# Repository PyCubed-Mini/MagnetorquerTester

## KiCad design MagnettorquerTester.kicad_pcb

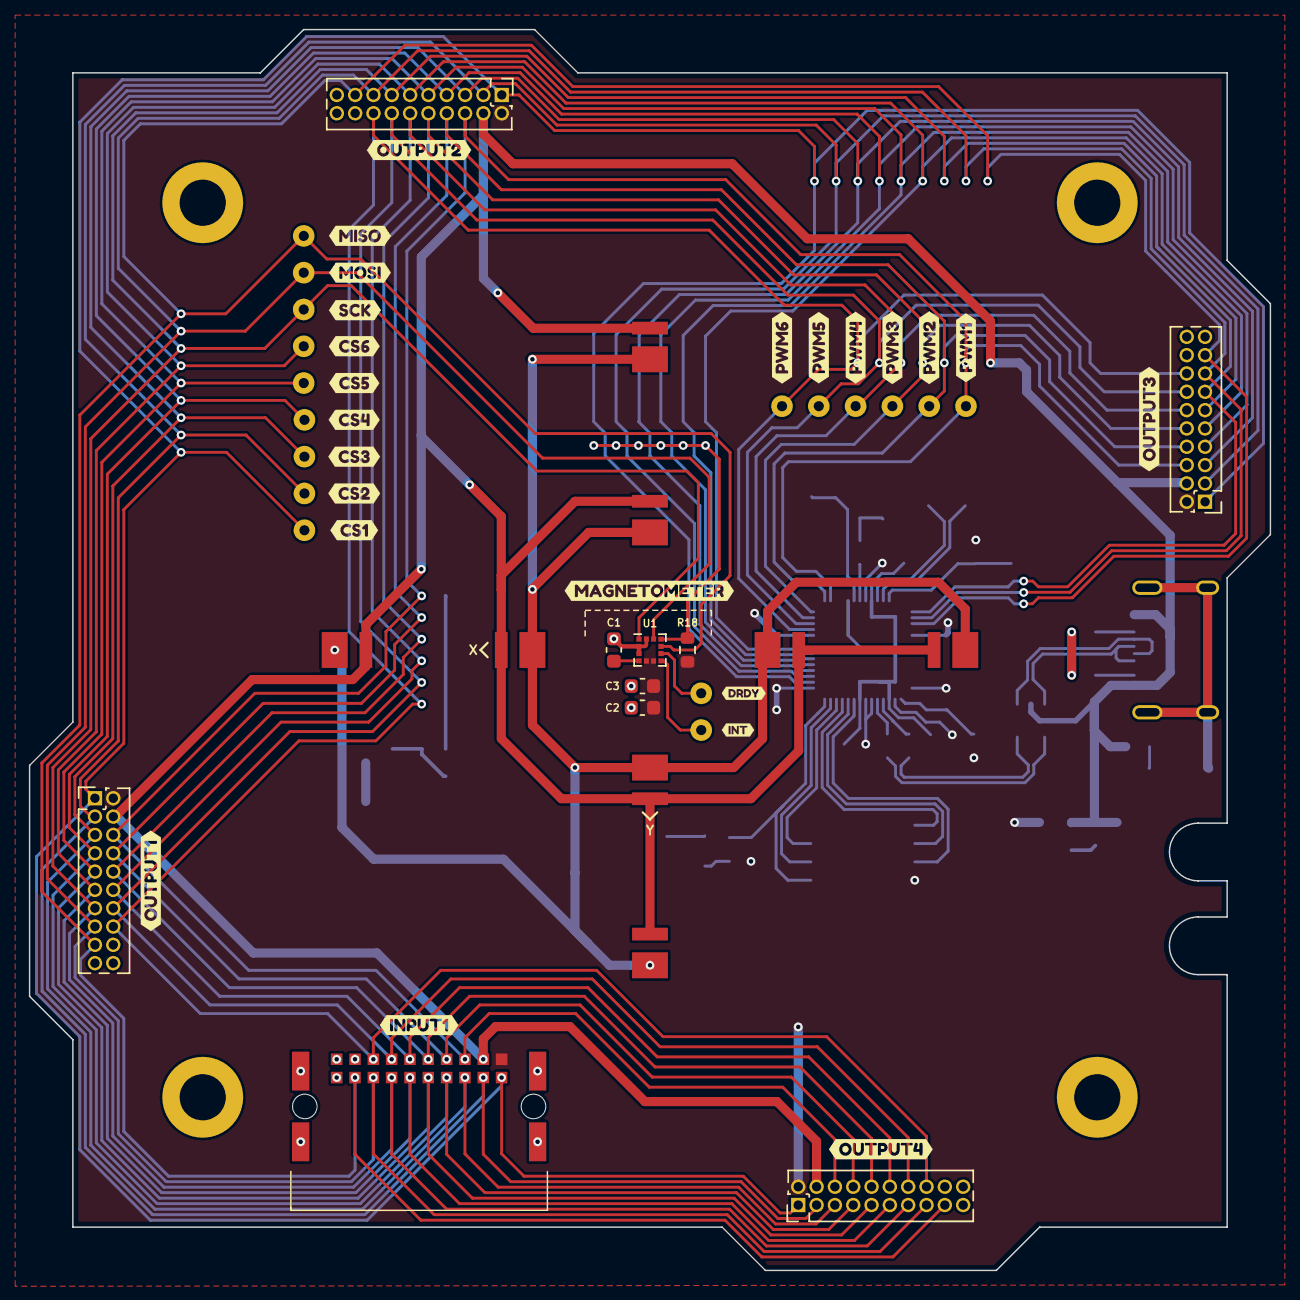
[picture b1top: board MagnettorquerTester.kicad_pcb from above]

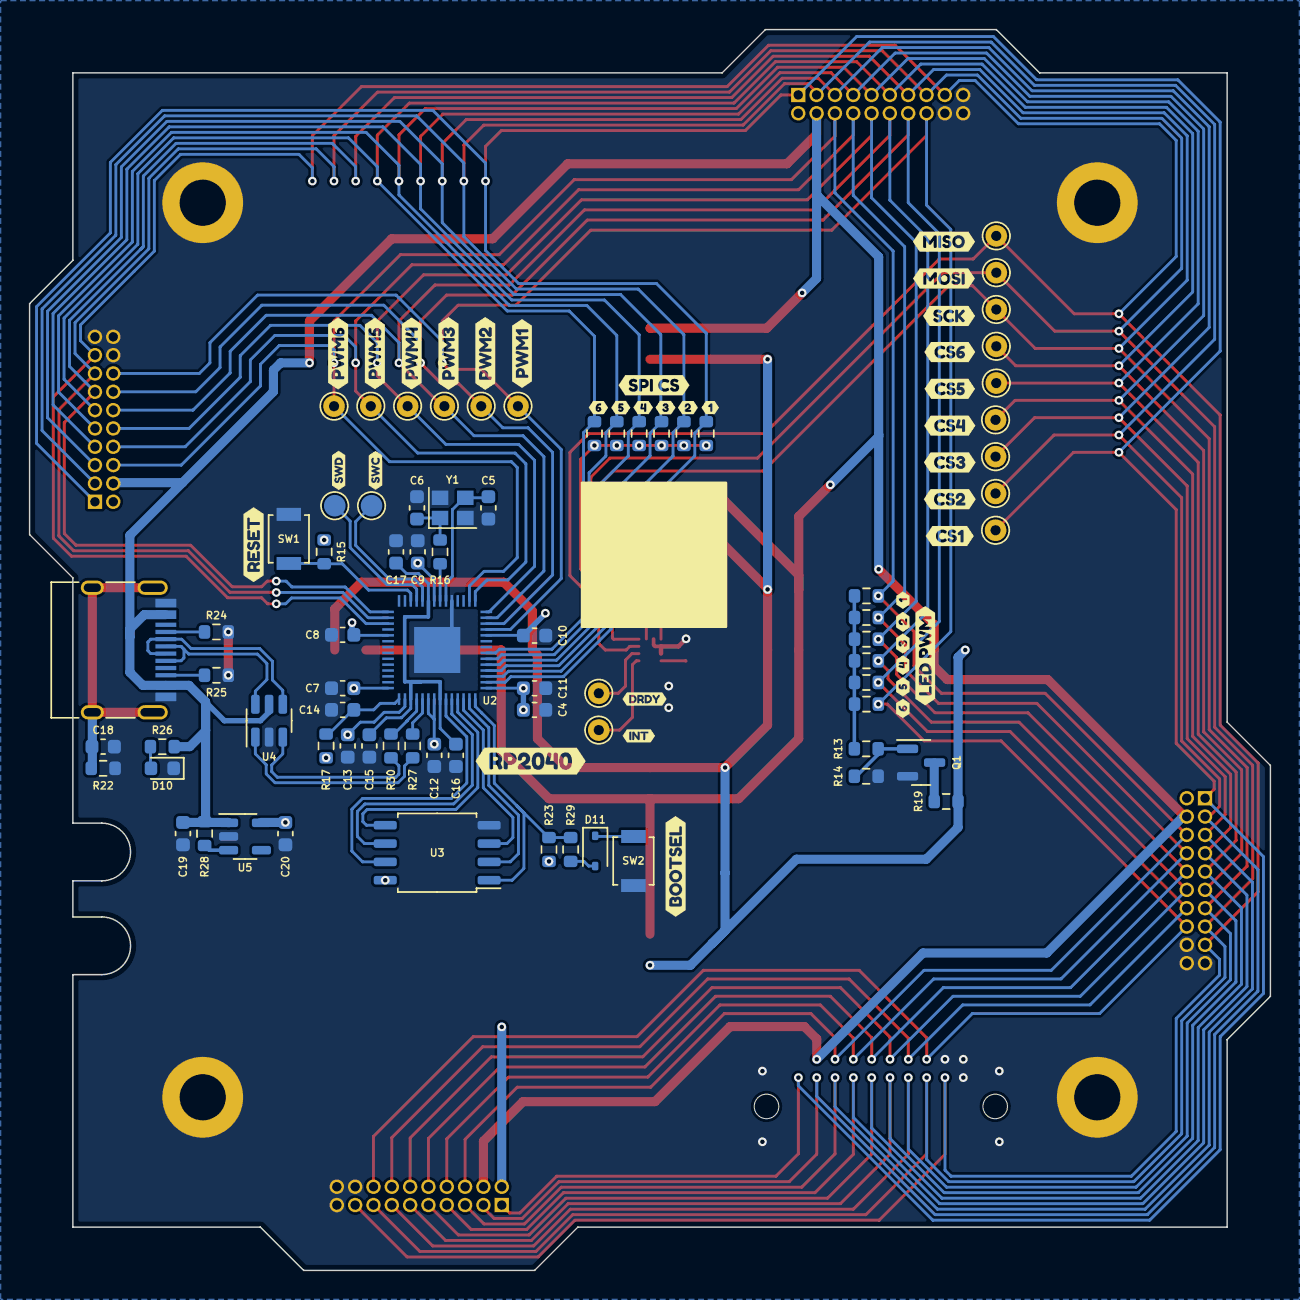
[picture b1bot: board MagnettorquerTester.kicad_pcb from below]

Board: 2 copper layers, 86.0 x 86.0 mm, 156 parts (111 on the bottom side), 53 nets.

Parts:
C1, C3, C7, C8, C9, C10, C11, C12, C13, C16, C17: 0.1uF; C_0603_1608Metric
C2, C4, C14, C15, C19, C20: 1uF; C_0603_1608Metric
C5, C6: 22pF; C_0603_1608Metric
C18: 4.7nF; C_0603_1608Metric
D1, D2, D3, D4, D5, D6, D7, D8: White; LED_WL-SWTP_WRE
D10: Green; LED_0603_1608Metric
D11: D_Schottky; D_SOD-323
H1, H2, H3, H4: MountingHole_Pad; MountingHole_3.2mm_M3_DIN965_Pad
J1: Out Conn 1; PinHeader_2x10_P1.27mm_Vertical
J2: Out Conn 2; PinHeader_2x10_P1.27mm_Vertical
J3: Out Conn 3; PinHeader_2x10_P1.27mm_Vertical
J4: Out Conn 4; PinHeader_2x10_P1.27mm_Vertical
J5: In Conn; M556102042R
J6: USB-C Receptacle; USB_C_Receptacle_HRO_TYPE-C-31-M-12
Q1: BSS138; SOT-23
R1, R2, R3, R4, R5, R6, R7, R8, R9, R10, R11, R12, R17, R19: 0; R_0603_1608Metric
R13: 220; R_0603_1608Metric
R14, R15, R18, R23: 10K; R_0603_1608Metric
R16, R26, R29: 1K; R_0603_1608Metric
R22: 1M; R_0603_1608Metric
R24, R25: 5.1K; R_0603_1608Metric
R27, R30: 27.4; R_0603_1608Metric
R28: 100K; R_0603_1608Metric
Ref**: Val**; pycubed_mini_half
SW1: Reset; SW_SPST_B3U-1000P
SW2: BOOTSEL; SW_SPST_B3U-1000P
TP1: INT; TestPoint_THTPad_D1.5mm_Drill0.7mm
TP2: DRDY; TestPoint_THTPad_D1.5mm_Drill0.7mm
TP3: PWM1; TestPoint_THTPad_D1.5mm_Drill0.7mm
TP4: PWM2; TestPoint_THTPad_D1.5mm_Drill0.7mm
TP5: PWM3; TestPoint_THTPad_D1.5mm_Drill0.7mm
TP6: PWM4; TestPoint_THTPad_D1.5mm_Drill0.7mm
TP7: PWM5; TestPoint_THTPad_D1.5mm_Drill0.7mm
TP8: PWM6; TestPoint_THTPad_D1.5mm_Drill0.7mm
TP9: SPI_SCK; TestPoint_THTPad_D1.5mm_Drill0.7mm
TP10: SPI_MOSI; TestPoint_THTPad_D1.5mm_Drill0.7mm
TP11: SPI_MISO; TestPoint_THTPad_D1.5mm_Drill0.7mm
TP12: SPI_CS1; TestPoint_THTPad_D1.5mm_Drill0.7mm
TP13: SPI_CS2; TestPoint_THTPad_D1.5mm_Drill0.7mm
TP14: SPI_CS3; TestPoint_THTPad_D1.5mm_Drill0.7mm
TP15: SPI_CS4; TestPoint_THTPad_D1.5mm_Drill0.7mm
TP16: SPI_CS5; TestPoint_THTPad_D1.5mm_Drill0.7mm
TP17: SPI_CS6; TestPoint_THTPad_D1.5mm_Drill0.7mm
TP18: SWCLK; TestPoint_Pad_D1.5mm
TP19: SWDIO; TestPoint_Pad_D1.5mm
U1: LIS3MDL; LGA-12_2x2mm_P0.5mm
U2: RP2040; IC57_RP2040
U3: W25Q32JVSS; SOIC-8_5.23x5.23mm_P1.27mm
U4: USBLC6-2SC6; SOT-23-6
U5: AP2112K-3.3; SOT-23-5
Y1: 12MHz; Crystal_SMD_2520-4Pin_2.5x2.0mm
kibuzzard-64532B72: G***; kibuzzard-64532B72
kibuzzard-64532BB5, kibuzzard-64532BB5#2: G***; kibuzzard-64532BB5
kibuzzard-64532BBA, kibuzzard-64532BBA#2: G***; kibuzzard-64532BBA
kibuzzard-64532BCA, kibuzzard-64532BCA#2: G***; kibuzzard-64532BCA
kibuzzard-64532BCE, kibuzzard-64532BCE#2: G***; kibuzzard-64532BCE
kibuzzard-64532BD1, kibuzzard-64532BD1#2: G***; kibuzzard-64532BD1
kibuzzard-64532BD5, kibuzzard-64532BD5#2: G***; kibuzzard-64532BD5
kibuzzard-64532C69: G***; kibuzzard-64532C69
kibuzzard-64532E75: G***; kibuzzard-64532E75
kibuzzard-64532FC8: G***; kibuzzard-64532FC8
kibuzzard-64532FCD: G***; kibuzzard-64532FCD
kibuzzard-645310D5, kibuzzard-645310D5#2: G***; kibuzzard-645310D5
kibuzzard-645321C3, kibuzzard-645321C3#2: G***; kibuzzard-645321C3
kibuzzard-645321D8, kibuzzard-645321D8#2: G***; kibuzzard-645321D8
kibuzzard-645321E4, kibuzzard-645321E4#2: G***; kibuzzard-645321E4
kibuzzard-645321EC, kibuzzard-645321EC#2: G***; kibuzzard-645321EC
kibuzzard-645321F5, kibuzzard-645321F5#2: G***; kibuzzard-645321F5
kibuzzard-645321FE, kibuzzard-645321FE#2: G***; kibuzzard-645321FE
kibuzzard-645322DE, kibuzzard-645322DE#2: G***; kibuzzard-645322DE
kibuzzard-645323A0, kibuzzard-645323A0#2: G***; kibuzzard-645323A0
kibuzzard-645323A5, kibuzzard-645323A5#2: G***; kibuzzard-645323A5
kibuzzard-645333A6: G***; kibuzzard-645333A6
kibuzzard-6453239A, kibuzzard-6453239A#2: G***; kibuzzard-6453239A
kibuzzard-6453269D: G***; kibuzzard-6453269D
kibuzzard-6453278C, kibuzzard-6453278C#2: G***; kibuzzard-6453278C
kibuzzard-6453285D: G***; kibuzzard-6453285D
kibuzzard-6453286D: G***; kibuzzard-6453286D
kibuzzard-64531072, kibuzzard-64531072#2: G***; kibuzzard-64531072
kibuzzard-64532206, kibuzzard-64532206#2: G***; kibuzzard-64532206
kibuzzard-64532321: G***; kibuzzard-64532321
kibuzzard-64532386, kibuzzard-64532386#2: G***; kibuzzard-64532386
kibuzzard-64532395, kibuzzard-64532395#2: G***; kibuzzard-64532395
kibuzzard-64532783, kibuzzard-64532783#2: G***; kibuzzard-64532783
kibuzzard-64532824: G***; kibuzzard-64532824
kibuzzard-64532894: G***; kibuzzard-64532894
kibuzzard-64533294: G***; kibuzzard-64533294

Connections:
+1V1: C15.1, C16.1, C17.1, U2.23 (DVDD), U2.45 (VREG_VOUT), U2.50 (DVDD)
+3V3: C2.1, C3.1, C4.1, C7.1, C8.1, C9.1, C10.1, C11.1, C12.1, C13.1, C20.1, J1.2, J2.2, J3.2, J4.2, J5.2, R15.1, R17.2, R18.1, R23.1, U1.5 (Vdd), U1.6 (Vdd_IO), U2.1 (IOVDD), U2.10 (IOVDD), U2.22 (IOVDD), U2.33 (IOVDD), U2.42 (IOVDD), U2.44 (VREG_VIN), U2.48 (USB_VDD), U2.49 (IOVDD), U3.8 (VCC), U5.5 (VOUT)
/AREF: C14.2, R17.1, U2.43 (ADC_AVDD)
/DRDY: TP2.1, U1.8 (DRDY)
/INT: TP1.1, U1.7 (INT)
/PWM: R7.2, R8.2, R9.2, R10.2, R11.2, R12.2, R13.1
/PWM1: J1.6, J2.6, J3.6, J4.6, J5.6, R7.1, TP3.1, U2.16 (GPIO13)
/PWM2: J1.8, J2.8, J3.8, J4.8, J5.8, R8.1, TP4.1, U2.15 (GPIO12)
/PWM3: J1.10, J2.10, J3.10, J4.10, J5.10, R9.1, TP5.1, U2.14 (GPIO11)
/PWM4: J1.12, J2.12, J3.12, J4.12, J5.12, R10.1, TP6.1, U2.13 (GPIO10)
/PWM5: J1.14, J2.14, J3.14, J4.14, J5.14, R11.1, TP7.1, U2.12 (GPIO9)
/PWM6: J1.16, J2.16, J3.16, J4.16, J5.16, R12.1, TP8.1, U2.11 (GPIO8)
/QSPI_CS: R23.2, R29.1, U2.56 (QSPI_CSN), U3.1 (~CS)
/QSPI_DATA0: U2.53 (QSPI_SD0), U3.5 (DI(IO0))
/QSPI_DATA1: U2.55 (QSPI_SD1), U3.2 (DO(IO1))
/QSPI_DATA2: U2.54 (QSPI_SD2), U3.3 (IO2)
/QSPI_DATA3: U2.51 (QSPI_SD3), U3.7 (IO3)
/QSPI_SCK: U2.52 (QSPI_SCLK), U3.6 (CLK)
/RESET: R15.2, SW1.2 (B), U2.26 (RUN)
/SPI_CS: R1.2, R2.2, R3.2, R4.2, R5.2, R6.2, R18.2, U1.10 (~CS)
/SPI_CS1: J1.1, J2.1, J3.1, J4.1, J5.1, R1.1, TP12.1, U2.2 (GPIO0)
/SPI_CS2: J1.3, J2.3, J3.3, J4.3, J5.3, R2.1, TP13.1, U2.3 (GPIO1)
/SPI_CS3: J1.5, J2.5, J3.5, J4.5, J5.5, R3.1, TP14.1, U2.4 (GPIO2)
/SPI_CS4: J1.7, J2.7, J3.7, J4.7, J5.7, R4.1, TP15.1, U2.5 (GPIO3)
/SPI_CS5: J1.9, J2.9, J3.9, J4.9, J5.9, R5.1, TP16.1, U2.6 (GPIO4)
/SPI_CS6: J1.11, J2.11, J3.11, J4.11, J5.11, R6.1, TP17.1, U2.7 (GPIO5)
/SPI_MISO: J1.17, J2.17, J3.17, J4.17, J5.17, TP11.1, U1.9 (SDO/SA1), U2.31 (GPIO20)
/SPI_MOSI: J1.15, J2.15, J3.15, J4.15, J5.15, TP10.1, U1.11 (SDA/SDI/SDO), U2.30 (GPIO19)
/SPI_SCK: J1.13, J2.13, J3.13, J4.13, J5.13, TP9.1, U1.1 (SCL/SPC), U2.29 (GPIO18)
/SWCLK: TP18.1, U2.24 (SWCLK)
/SWDIO: TP19.1, U2.25 (SWD)
DBus+: J6.A6 (D+), J6.B6 (D+), U4.6 (I/O1)
DBus-: J6.A7 (D-), J6.B7 (D-), U4.4 (I/O2)
DM: R30.2, U2.46 (USB_DM)
DP: R27.1, U2.47 (USB_DP)
GND: C1.2, C2.2, C3.2, C4.2, C5.1, C6.1, C7.2, C8.2, C9.2, C10.2, C11.2, C12.2, C13.2, C14.1, C15.2, C16.2, C17.2, C18.1, C19.2, C20.2, D10.1 (K), H1.1, H2.1, H3.1, H4.1, J1.18, J1.19, J1.20, J2.18, J2.19, J2.20, J3.18, J3.19, J3.20, J4.18, J4.19, J4.20, J5.18, J5.19, J5.20, J5.MP (MountPin), J6.A1 (GND), J6.A12 (GND), J6.B1 (GND), J6.B12 (GND), Q1.2 (S), R14.1, R22.2, R24.1, R25.1, SW1.1 (A), SW2.2 (B), U1.2 (GND), U1.3 (GND), U1.12 (GND), U2.19 (TESTEN), U2.57 (GND), U3.4 (GND), U4.2 (GND), U5.2 (GND), Y1.2, Y1.4
unnamed: C6.2, R16.1, Y1.1
unnamed: D1.1 (K), D2.1 (K), D3.1 (K), D4.1 (K), D5.1 (K), D6.1 (K), D7.1 (K), D8.1 (K), R19.2
unnamed: D10.2 (A), R26.2
unnamed: D11.2 (A), R29.2
unnamed: D11.1 (K), SW2.1 (A)
unnamed: J6.A5 (CC1), R24.2
unnamed: J6.B5 (CC2), R25.2
unnamed: C18.2, J6.S1 (SHIELD), R22.1
unnamed: Q1.3 (D), R19.1
unnamed: Q1.1 (G), R13.2, R14.2
unnamed: R27.2, U4.1 (I/O1)
unnamed: R30.1, U4.3 (I/O2)
unnamed: C1.1, U1.4 (C1)
unnamed: C5.2, U2.20 (XIN), Y1.3
unnamed: R16.2, U2.21 (XOUT)
unnamed: R28.2, U5.3 (EN)
VBUS: C19.1, D1.2 (A), D2.2 (A), D3.2 (A), D4.2 (A), D5.2 (A), D6.2 (A), D7.2 (A), D8.2 (A), J1.4, J2.4, J3.4, J4.4, J5.4, J6.A4 (VBUS), J6.A9 (VBUS), J6.B4 (VBUS), J6.B9 (VBUS), R26.1, R28.1, U4.5 (VBUS), U5.1 (VIN)

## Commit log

2023-05-04 File Upload
2023-05-04 Exported BOM
2023-05-09 Added slots for USB cables
2023-05-26 Some silkscreen stuff
2023-06-07 Stash changes
